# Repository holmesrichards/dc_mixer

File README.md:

## AO DC Mixer

This is a DC coupled 3-input mixer, designed mainly for mixing control voltage signals. It is based loosely on the MFOS Quad DC mixer (but only one unit per module). A lot has been changed:

* For a general gain control, split MFOS's first op amp stage into an inverting variable gain mixing stage and an inverting unity gain with bias stage. This means MFOS's normal output became the inverted output and vice versa.
* In Wilson's design, bias was applied to stage with 3 summed inputs so output was -(V<sub>1</sub>+V<sub>2</sub>+V<sub>3</sub>)+4V<sub>bias</sub>, so he needed 4V<sub>bias</sub> going into the last stage to get output of (V<sub>1</sub>+V<sub>2</sub>+V<sub>3</sub>)+4V<sub>bias</sub>. Hence the gain of 4 on the bias amplification stage. Here the sum is separated from the bias, so bias stage output is -(V<sub>1</sub>+V<sub>2</sub>+V<sub>3</sub>)+2V<sub>bias</sub>. Therefore changed gain from 4 to 2. Also, to get same offset range, changed the offset voltage divider to divide by 2, not 4.
* Added antiparallel diodes and a pulldown resistor in the offset voltage divider, a la YuSynth mixer. This and the small value resistors makes the response to the offset knob knob S shaped, with a flat region around 0 V, reaching about ±10.2 V offset at extreme ends. 
 
Note, if rails are asymmetric it shifts the inflection point horizontally but *not* vertically, which is great! -12 V and +11 V by simulation gives an S centered at about 48% pot position and 0 V.
* Reduced impedances in most stages.

## Current draw
9 mA +12 V, 9 mA -12 V

## Documentation

* [Build notes and calibration](Docs/build_notes.md) 
* [Schematic](Docs/ao_dc_mixer.pdf)
* [BOM](Docs/ao_dc_mixer_bom.pdf)

Repo uses submodules aoKicad and Kosmo_panel. To clone:

```
git clone git@github.com:holmesrichards/dc_mixer.git
git submodule init
git submodule update
```

Alternatively do

```
git clone --recurse-submodules git@github.com:holmesrichards/dc_mixer.git
```

Or if you download the repository as a zip file, you must also click on the "aoKicad" and "Kosmo\_panel" links on the GitHub page (they'll have "@ something" after them) and download them as separate zip files which you can unzip into this repo's aoKicad and Kosmo\_panel directories.

If desired, copy the files from aoKicad and Kosmo\_panel to wherever you prefer (your KiCad user library directory, for instance, if you have one). Then in KiCad, add symbol libraries 

```
aoKicad/ao_symbols
Kosmo_panel/Kosmo
```
and footprint libraries 
```
aoKicad/ao_tht
Kosmo_panel/Kosmo_panel.
```

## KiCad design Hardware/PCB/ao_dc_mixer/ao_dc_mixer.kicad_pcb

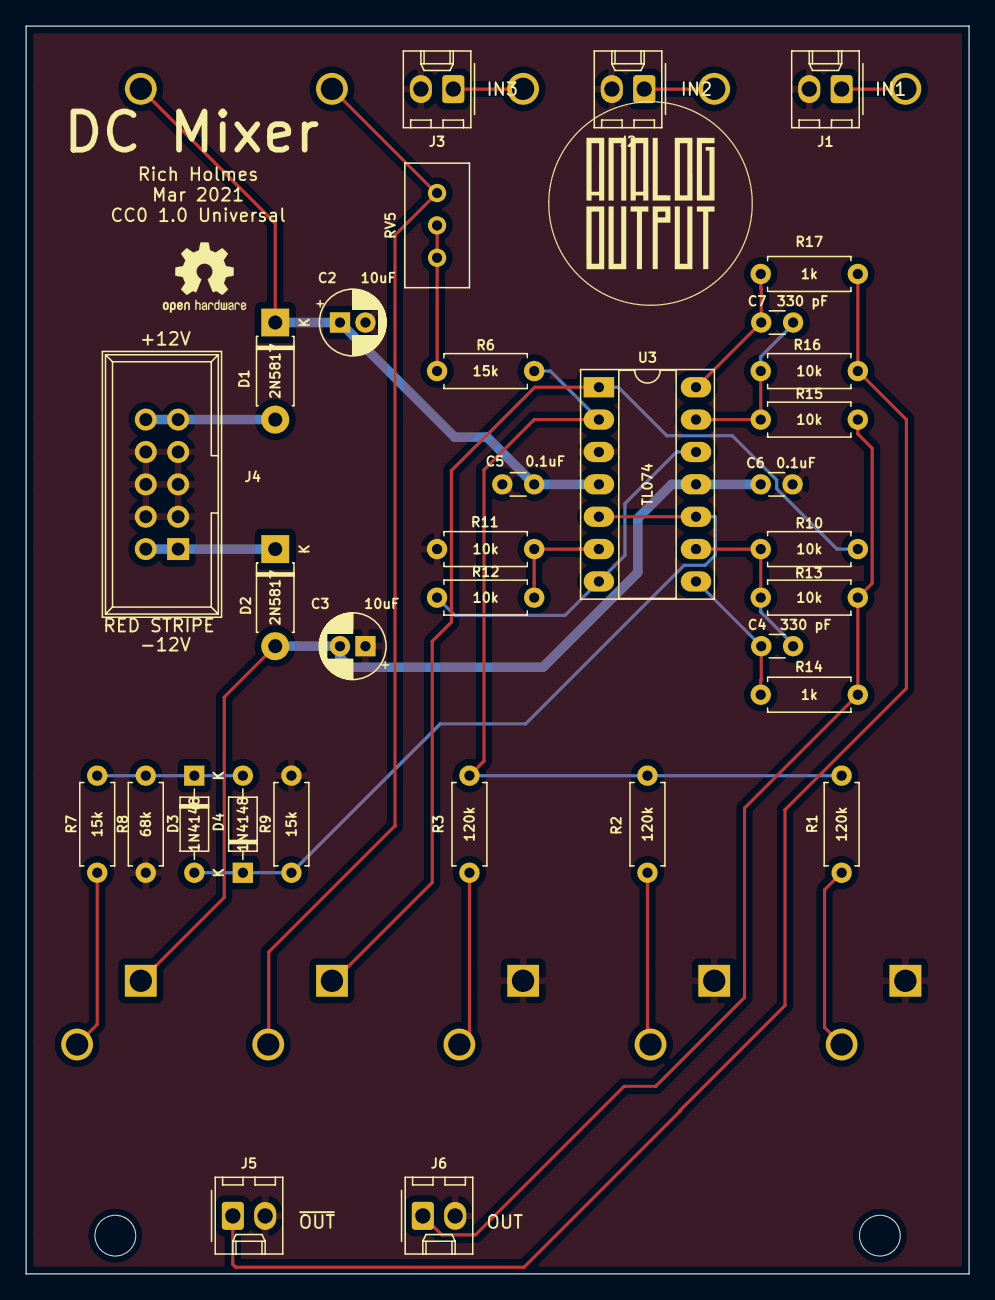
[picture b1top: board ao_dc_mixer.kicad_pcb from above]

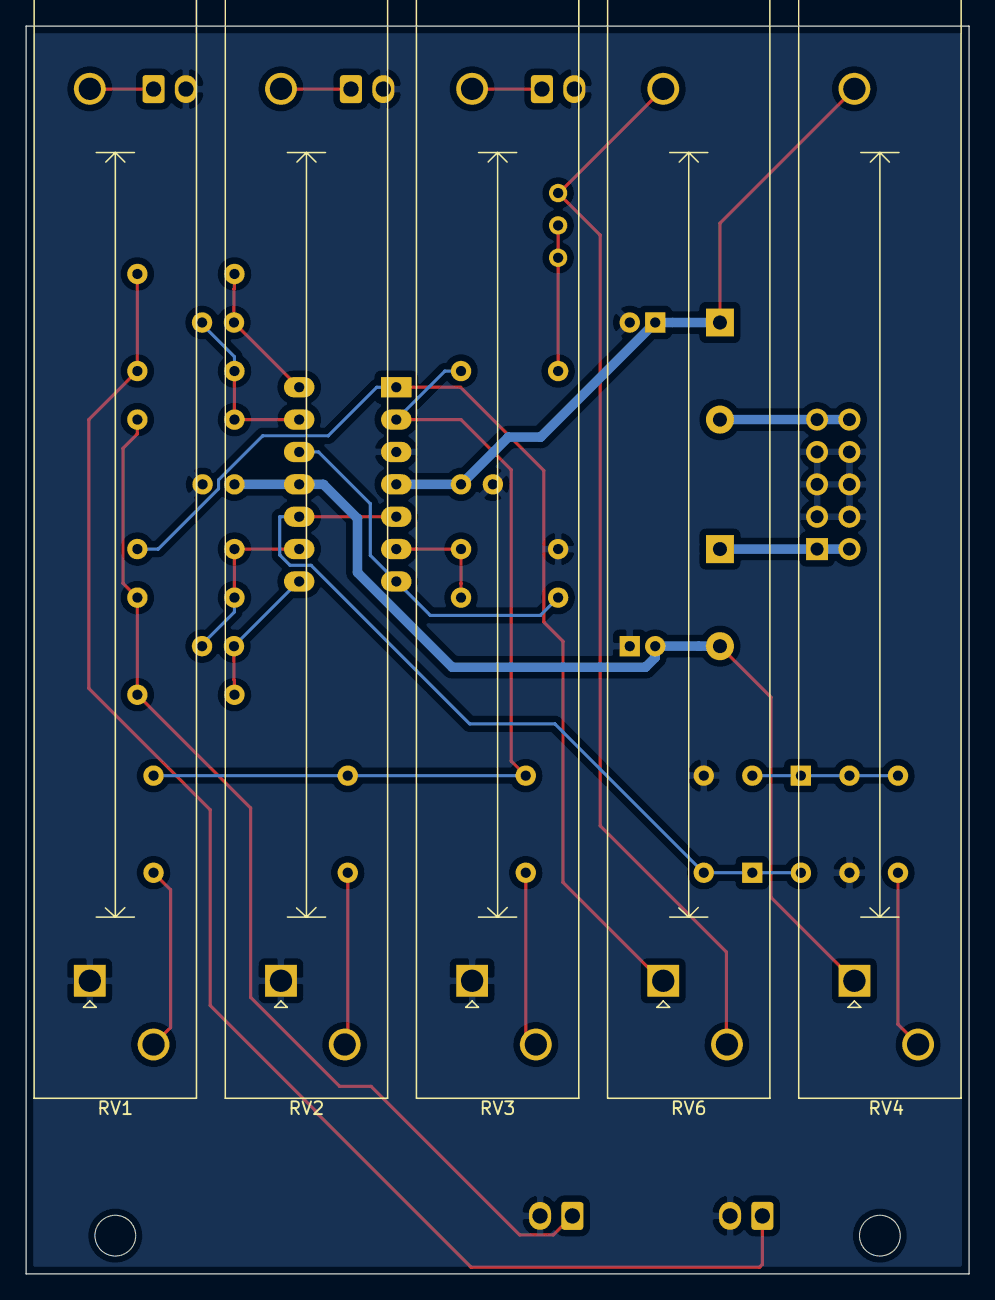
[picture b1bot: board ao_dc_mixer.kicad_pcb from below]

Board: 2 copper layers, 74.0 x 97.9 mm, 43 parts (5 on the bottom side), 26 nets.

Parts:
C2, C3: 10uF; CP_Radial_D5.0mm_P2.00mm
C4, C7: 330 pF; C_Disc_D3.0mm_W1.6mm_P2.50mm
C5, C6: 0.1uF; C_Disc_D3.0mm_W1.6mm_P2.50mm
D1, D2: 2N5817; D_DO-41_SOD81_P7.62mm_Horizontal
D3, D4: 1N4148; D_DO-35_SOD27_P7.62mm_Horizontal
GRAF1: AO Logo; analogoutput
GRAF2: OSHW Logo; OSHW-Logo2_7.3x6mm_SilkScreen
GRAF3: Panel holes; ao_dc_mixer_slide_holes
H1, H2: MountingHole; MountingHole_3.2mm_M3
J1, J2, J3, J5, J6: 2 Pin Molex Header; Molex_KK-254_AE-6410-02A_1x02_P2.54mm_Vertical
J4: Synth_power_2x5; Power_Header
R1, R2, R3: 120k; R_Axial_DIN0207_L6.3mm_D2.5mm_P7.62mm_Horizontal
R6, R7, R9: 15k; R_Axial_DIN0207_L6.3mm_D2.5mm_P7.62mm_Horizontal
R8: 68k; R_Axial_DIN0207_L6.3mm_D2.5mm_P7.62mm_Horizontal
R10, R11, R12, R13, R15, R16: 10k; R_Axial_DIN0207_L6.3mm_D2.5mm_P7.62mm_Horizontal
R14, R17: 1k; R_Axial_DIN0207_L6.3mm_D2.5mm_P7.62mm_Horizontal
RV1, RV2, RV3, RV4, RV6: B100k; Potentiometer_Alpha_RA6020F_Single_Slide
RV5: 10k; Potentiometer_Bourns_3296W_Vertical
U3: TL074; DIP-14_W7.62mm_Socket_LongPads

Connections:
+12V: C2.1, C5.1, D1.1, RV4.3, U3.4
-12V: C3.2, C6.2, D2.2, RV4.1, U3.11
/IN1: J1.1, RV1.3
/IN2: J2.1, RV2.3
/IN3: J3.1, RV3.3
/OUT: J6.1, R13.1, R14.1, R15.2
/V_BIAS: D3.2, D4.1, R9.1, U3.5, U3.10
/~OUT: J5.1, R16.1, R17.1
GND: C2.2, C3.1, C5.2, C6.1, J1.2, J2.2, J3.2, J4.3, J4.4, J4.5, J4.6, J4.7, J4.8, J5.2, J6.2, R8.2, R9.2, R11.2, RV1.1, RV2.1, RV3.1, U3.3
unnamed: C4.1, R10.1, R13.2, U3.9
unnamed: C4.2, R14.2, U3.8
unnamed: C7.1, R15.1, R16.2, U3.13
unnamed: C7.2, R17.2, U3.14
unnamed: D1.2, J4.9, J4.10
unnamed: D2.1, J4.1, J4.2
unnamed: D3.1, D4.2, R7.2, R8.1
unnamed: R1.1, R2.1, R3.1, R6.2, U3.2
unnamed: R1.2, RV1.2
unnamed: R2.2, RV2.2
unnamed: R3.2, RV3.2
unnamed: R6.1, RV5.2, RV5.3
unnamed: R7.1, RV4.2
unnamed: R10.2, RV6.1, U3.1
unnamed: R11.1, R12.2, U3.6
unnamed: R12.1, U3.7, U3.12
unnamed: RV5.1, RV6.2, RV6.3

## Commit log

2021-03-08 initial version
2021-03-12 PCB and panel design
2021-03-12 New image
2021-03-14 rm cap on first stage
2021-03-17 Various revisions, new DNF symbols
2021-04-01 Gerbers, BOM, final version before fabrication
2021-04-01 Create LICENSE
2021-04-01 Update schematic PDF
2021-04-10 BOM updates
2021-04-15 Documentation updates
2021-04-26 Build notes tweak
2021-07-29 sym-lib-table
2021-08-12 submodules
2021-08-12 submodule update
2021-08-21 relocate libraries
2021-08-21 rm project libraries
2021-08-27 submodule doc
2021-09-15 SVG decontamination
2021-12-24 Current draw
